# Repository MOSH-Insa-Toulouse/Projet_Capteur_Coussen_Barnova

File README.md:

# Projet_Capteur_Coussen_Barnova
 2021-2022
 Low-tech pencil drawn strain gauge sensor developed in 4th year Engineering Physics course MOSH (Microcontroller Open Source Hardware) at INSA (National Institute of Applied Sciences) Toulouse.

The project is inspired by Scientific Reports article "Pencil Drawn Strain Gauges and Chemiresistors on Paper" written by Cheng-Wei Lin, Zhibo Zhao, Jaemyung Kim & Jiaxing Huang. This article can be found in our repository.

The aim of this project is to fabricate a reliable strain gauge made of pencil drawn paper.

## Idea
Pencil carbon deposited on the paper is made of percolated graphite particles network where electrons move. Mechanism enabling electrons to move from grain to grain is tunnelling through potential barrier. However, tunnelling depends exponentially on the length of the barrier. When a mechanical stress is applied to the gauge, grains of percolated network spread away. Thus, when a tension is applied to gauge electrons move less => resistance increases. When gauge is compressed electrons move more => resistance decreases.

## Hardware implementation
A photo of our sensor can be found in the repository.

Supplying the sensor with 5V induces current in the sensor. However, this current has an order of magnitude of a nanoampere. Ordinary multimeter is not able to detect such a small current. We use LTC1050 amplifier which enables to convert current into a voltage that can be measured thanks to Arduino Uno board.
We dimensioned amplifier circuit in order to filter 50 Hz noise and cut off high frequencies. Further explanations are contained in Electronic_simulation_LTSpice document.
We designed this electrical circuit as a shield PCB (printed circuit board) using KiCad 6.0 software and printed it. KiCad files can be found in KiCad directory.

## Software implementation
With a focus on customized Arduino board we've written Arduino programs to run OLED screen, rotatory encoder and HC-O5 Bluetooth module enabling to send mesasured data to a smartphone. This code can be found in the directory "code_Arduino". To run the code you will need to download Adafruit_1306 library.
We developed this code without PCB and for the sake of simplicity and efficiency we changed one pin between PCB and code. Switch pin of the rotary encoder is wired to the pin 3 of Arduino instead of pin 5 (as in PCB). The reason is that we use Interrupts in the code and they can be generated only by the Arduino pins 2 and 3.  
Finally, we designed a simple app on MIT App Inventor that receives and plots the data. It can be found in the directory "App". Our app fails when it receives inf value and we did not eliminate this bug. 

## Tests and results

Our sensor can be drawn with different pencils. Their content is a mixture of clay and carbon. Pencils containing more clay are indicated with H meaning "high". Their stroke is light. Pencils containing more carbon are indicated with B meaning "low" and they draw bolder lines. Here is scale of pencils hardness.

Results can be found in the file Measures. We get linear slope of the calibration curve which confirms that resistance depends on strain. It is possible to make a sensor with pencil drawn paper. We note that sensibility of our sensor is the slope of the linear function - for HB it is 14 385 Mohms/m.
Even though, our sensor gives limited results, we measured how the resistance changes as a function of curvature and we are able to link it to bending. This explanation can be found in the document "Test bench". However, wires connection induced on paper a lot of error because of lack of stability.

## Limits 
Firstly, PCB oxydized which lead to its malfunction. Most probably, certain pins were connected with the pins they were not supposed to which hindered correct supply and transit.
Furthermore, resistance depends clearly on amount of carbon deposited. This factor is quite difficult to evaluate and to control in our conditions.
Moreover, our measures are not repeatable because paper distorts when we measure relatively big strain. 
Finally, wire connections slip on the paper which alters the resistance. We would need a more reliable connection to decrease average error and get more repeatable results. We could possibly imagine a solution to stabilize the position of the wires connections relatively to each other. 

## Authors
Sarah Barnová : barnova@insa-toulouse.fr
Louise Coussen : coussen@insa-toulouse.fr

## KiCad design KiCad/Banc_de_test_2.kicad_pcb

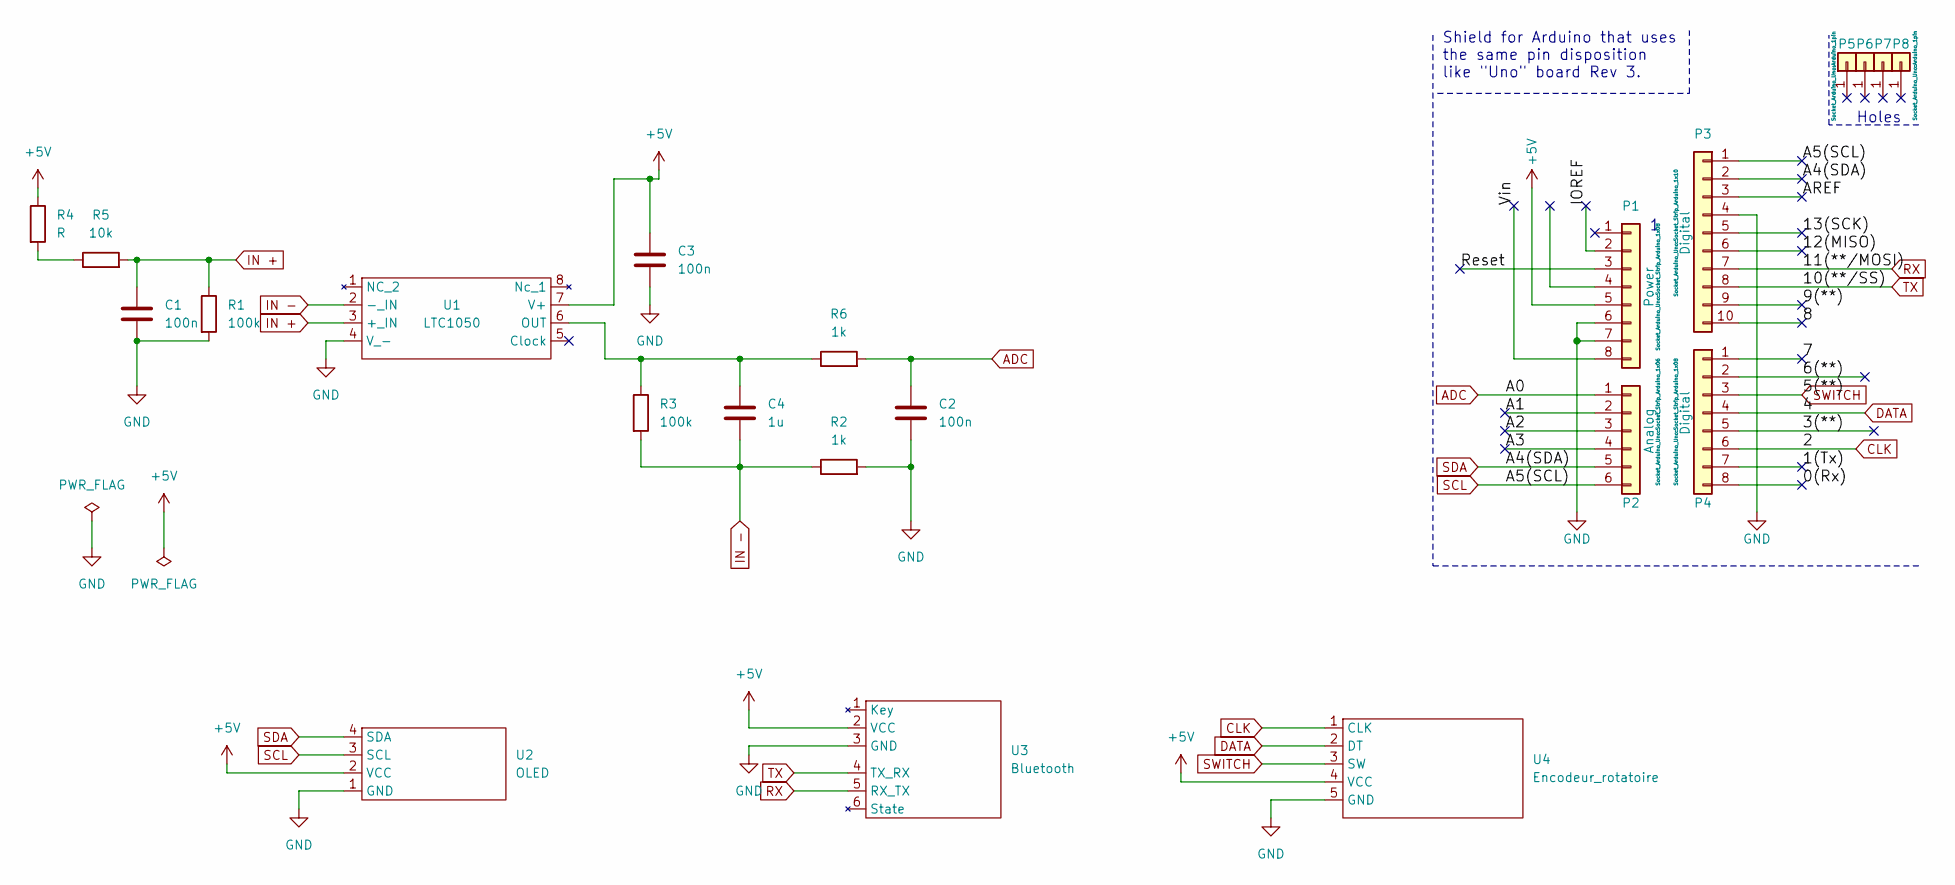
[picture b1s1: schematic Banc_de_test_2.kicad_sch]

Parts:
C1, C2, C3: 100n; C_Disc_D5.0mm_W2.5mm_P5.00mm
C4: 1u; C_Rect_L9.0mm_W5.1mm_P7.50mm_MKT
P1: Power; Socket_Strip_Arduino_1x08
P2: Analog; Socket_Strip_Arduino_1x06
P3: Digital; Socket_Strip_Arduino_1x10
P4: Digital; Socket_Strip_Arduino_1x08
P5, P6, P7, P8: CONN_01X01; Arduino_1pin
R1, R3: 100k; R_Axial_DIN0207_L6.3mm_D2.5mm_P7.62mm_Horizontal
R2, R6: 1k; R_Axial_DIN0207_L6.3mm_D2.5mm_P7.62mm_Horizontal
R4: R; R_Axial_DIN0207_L6.3mm_D2.5mm_P7.62mm_Horizontal
R5: 10k; R_Axial_DIN0207_L6.3mm_D2.5mm_P7.62mm_Horizontal
U1: LTC1050
U2: OLED
U3: Bluetooth
U4: Encodeur_rotatoire; Encodeur_rot

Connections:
+5V: C3.1, P1.5, R4.1, U1.7 (V+), U2.2 (VCC), U3.2 (VCC), U4.4 (VCC)
/0(Rx): P4.8
/1(Tx): P4.7
/3(**): P4.5
/6(**): P4.2
/7: P4.1
/8: P3.10
/9(**): P3.9
/12(MISO): P3.6
/13(SCK): P3.5
/A1: P2.2
/A2: P2.3
/A3: P2.4
/AREF: P3.3
/IOREF: P1.2
/Reset: P1.3
/Vin: P1.8
ADC: C2.1, P2.1, R6.2
CLK: P4.6, U4.1 (CLK)
DATA: P4.4, U4.2 (DT)
GND: C1.2, C2.2, C3.2, P1.6, P1.7, P3.4, R1.2, R2.2, U1.4 (V_-), U2.1 (GND), U3.3 (GND), U4.5 (GND)
IN +: C1.1, R1.1, R5.2, U1.3 (+_IN)
IN -: C4.2, R2.1, R3.2, U1.2 (-_IN)
unnamed: C4.1, R3.1, R6.1, U1.6 (OUT)
unnamed: R4.2, R5.1
RX: P3.7, U3.5 (RX_TX)
SCL: P2.6, P3.1, U2.3 (SCL)
SDA: P2.5, P3.2, U2.4 (SDA)
SWITCH: P4.3, U4.3 (SW)
TX: P3.8, U3.4 (TX_RX)

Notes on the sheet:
Holes
Shield for Arduino that uses the same pin disposition like "Uno" board Rev 3.

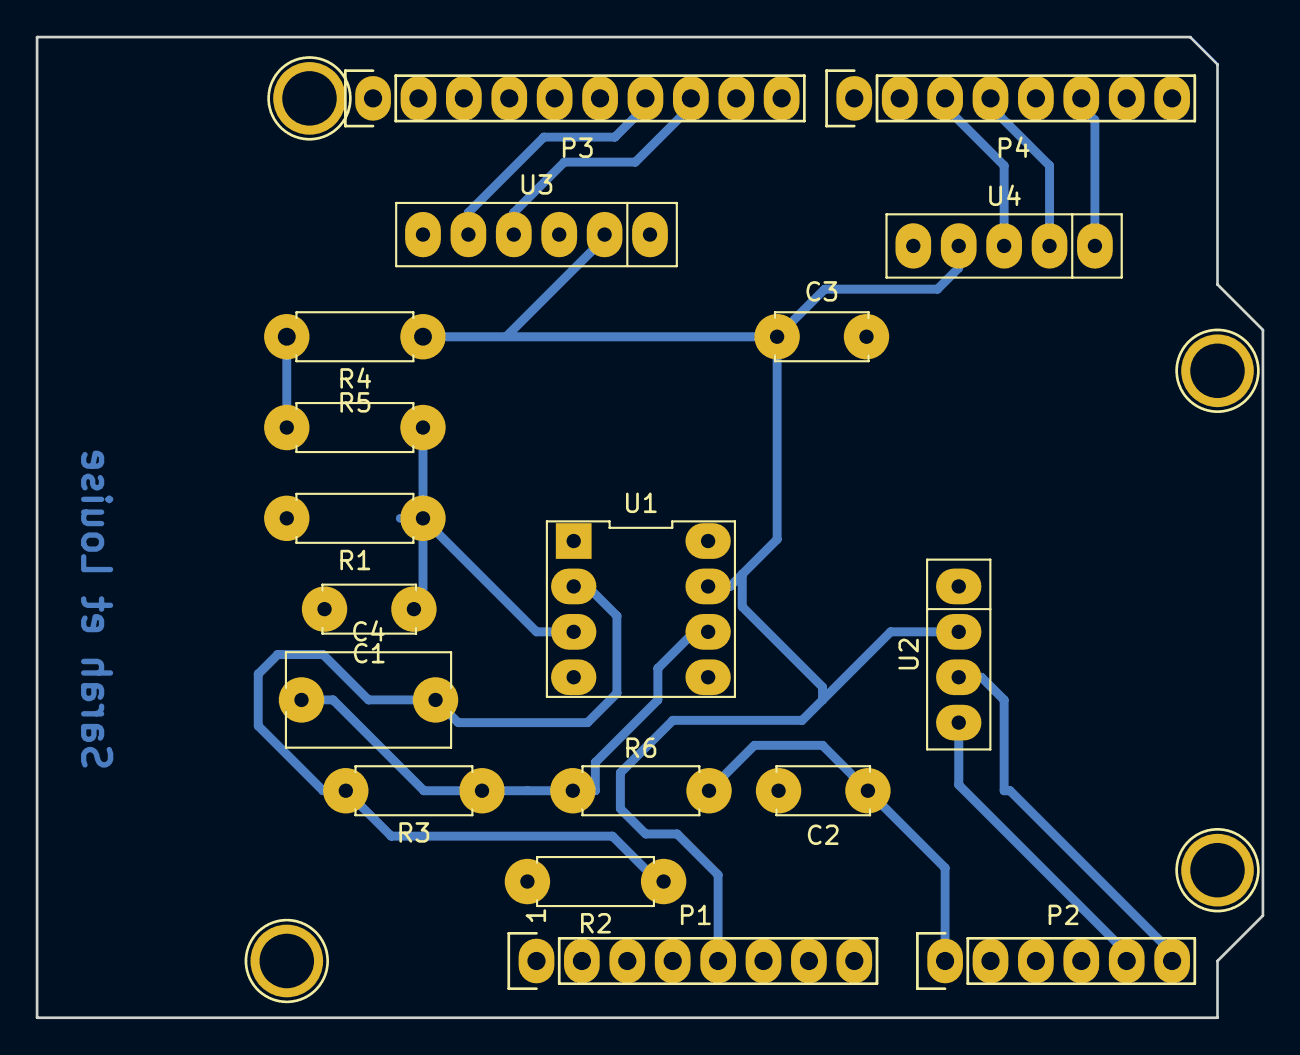
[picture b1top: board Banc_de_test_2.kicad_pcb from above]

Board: 2 copper layers, 68.6 x 54.9 mm, 22 parts (0 on the bottom side), 14 nets.

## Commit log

2022-04-15 Create fp-info-cache
2022-04-16 Create fp-lib-table
2022-04-16 Create sym-lib-table
2022-04-16 Electronic_circuit_design.pdf
    This document comments electronic design. Main focus is on filters and cut-off frequencies
